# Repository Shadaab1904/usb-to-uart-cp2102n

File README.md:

# usb-to-uart-cp2102n
KiCad project: USB to UART converter based on CP2102N
This is a simple USB to UART converter board designed in **KiCad**, built around the **CP2102N** USB-to-Serial bridge IC.

## ✏️ About
This project converts USB signals to standard UART (TX, RX) levels, making it easy to interface a computer to microcontrollers, sensors, and other serial devices.  

It includes:
- CP2102N USB-to-UART IC
- USB connector (e.g., USB-C)
- Status LEDs (TX/RX)
- Filter capacitors
- UART header pins (TX, RX, , RST, GND, etc.)

## 📂 Project structure
- `USB TO UART.kicad_sch` – Schematic file
- `usb-to-uart.kicad_pcb` – PCB layout file
- `usb-to-uart.kicad_pro` – KiCad project file
- `symbols/` – Custom schematic symbols 
- `STEP/` - USB Type-C 3D Model
- `gerber/` – Gerber and drill files for fabrication
- `bom.csv` – Bill of Materials

- ## ⚙️ Tools
- Designed with [KiCad](https://kicad.org/)

- ## 📦 Fabrication
Use the files in the `gerber/` directory to order PCBs from manufacturers (e.g., JLCPCB etc.).

## 💡 Features
- CP2102N supports full-speed USB 2.0
- The CP2102N receives power from USB VBUS (5 V), connected to the REGIN pin. Its internal 3.3 V regulator outputs on VDD, with a 100 nF decoupling capacitor. This VDD rail powers the chip and defines the logic level for all UART signals (TX, RX, etc). Therefore, the UART interface operates at standard 3.3 V logic levels.
- Status LEDs for data transmission/reception
- Compact 2-layer PCB

- ## 📄 License
MIT License – feel free to modify and use.

## 🙌 Contributions
Pull requests welcome! If you spot issues or have improvements, please open an issue or PR.

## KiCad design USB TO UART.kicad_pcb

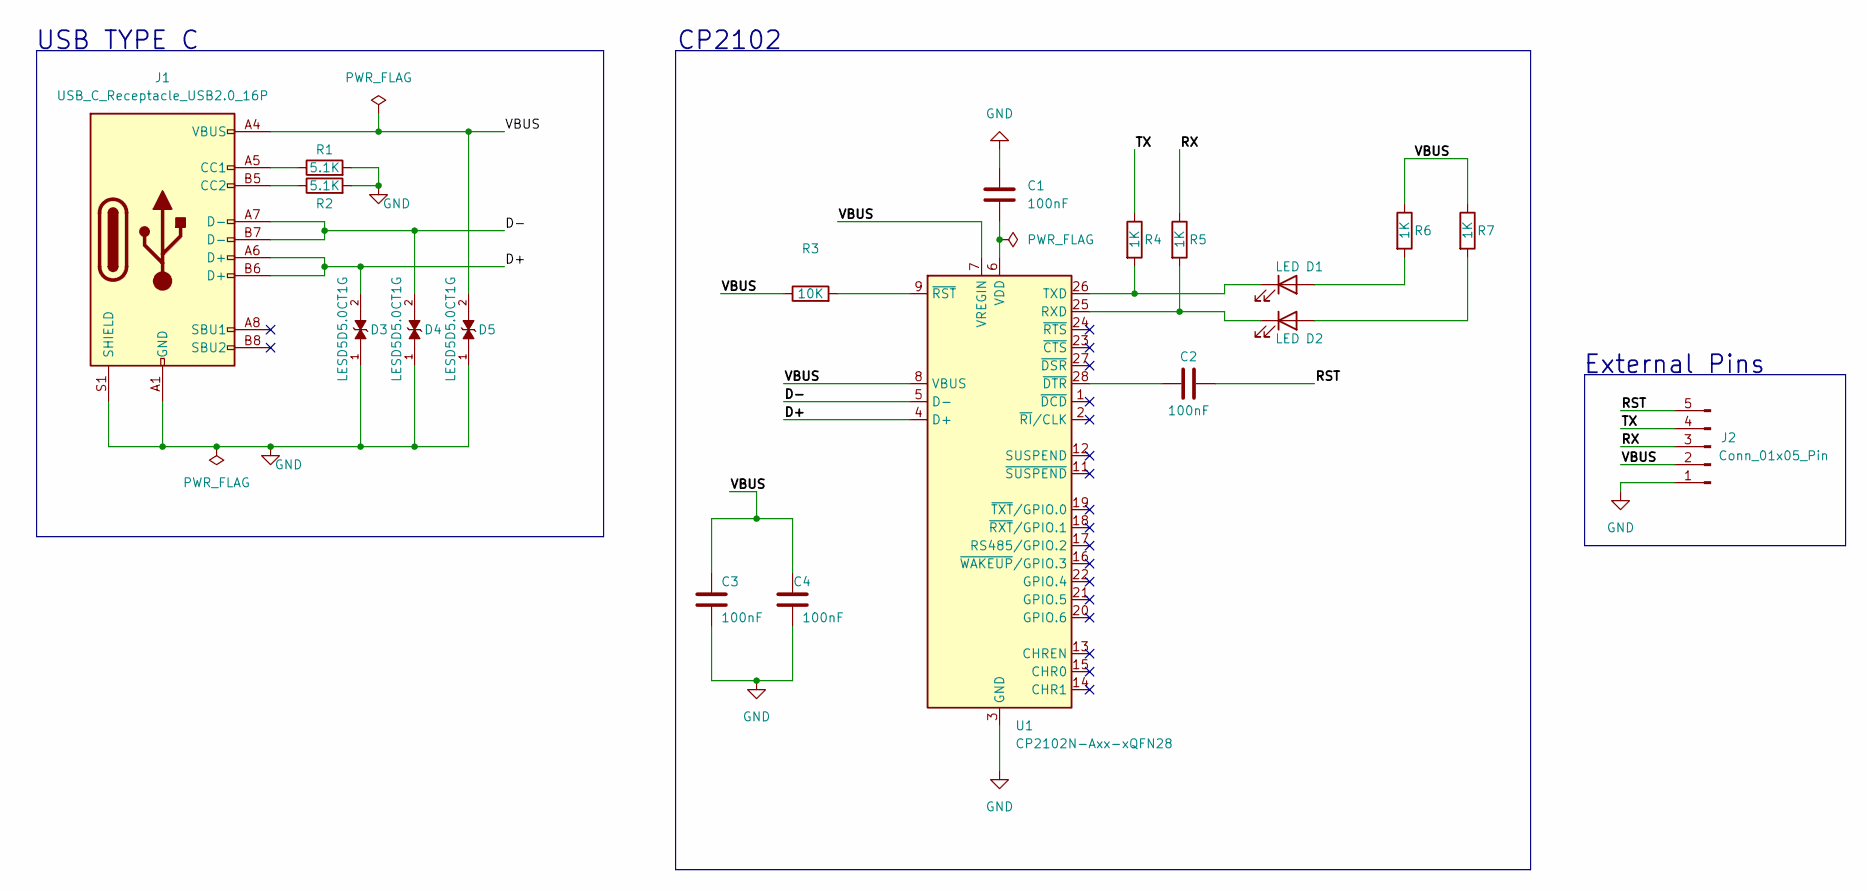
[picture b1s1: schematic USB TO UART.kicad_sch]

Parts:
C1, C2, C3, C4: 100nF; C_0805_2012Metric
D1, D2: LED; LED_0603_1608Metric
D3, D4, D5: LESD5D5.0CT1G; TVS_LESD5D5.0CT1G; PARTREV O
J1: USB_C_Receptacle_USB2.0_16P; USB_C_Receptacle_HRO_TYPE-C-31-M-12
J2: Conn_01x05_Pin; PinHeader_1x05_P2.54mm_Horizontal
R1, R2: 5.1K; R_0402_1005Metric
R3: 10K; R_0402_1005Metric
R4, R5, R6, R7: 1K; R_0402_1005Metric
U1: CP2102N-Axx-xQFN28; QFN-28-1EP_5x5mm_P0.5mm_EP3.35x3.35mm

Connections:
/D+: D3.2, J1.A6 (D+), J1.B6 (D+), U1.4 (D+)
/D-: D4.2, J1.A7 (D-), J1.B7 (D-), U1.5 (D-)
/RST: C2.2, J2.5
/RX: J2.3, R5.1
/TX: J2.4, R4.1
/VBUS: C3.1, C4.1, D5.2, J1.A4 (VBUS), J1.A9 (VBUS), J1.B4 (VBUS), J1.B9 (VBUS), J2.2, R3.1, R6.1, R7.1, U1.7 (VREGIN), U1.8 (VBUS)
GND: C1.1, C3.2, C4.2, D3.1, D4.1, D5.1, J1.A1 (GND), J1.A12 (GND), J1.B1 (GND), J1.B12 (GND), J1.S1 (SHIELD), J2.1, R1.2, R2.2, U1.3 (GND), U1.29 (GND)
unnamed: D1.2 (A), R6.2
unnamed: D1.1 (K), R4.2, U1.26 (TXD)
unnamed: D2.2 (A), R7.2
unnamed: D2.1 (K), R5.2, U1.25 (RXD)
unnamed: J1.A5 (CC1), R1.1
unnamed: J1.B5 (CC2), R2.1
unnamed: C1.2, U1.6 (VDD)
unnamed: C2.1, U1.28 (~DTR)
unnamed: R3.2, U1.9 (~RST)

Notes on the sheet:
USB TYPE C
External Pins
CP2102

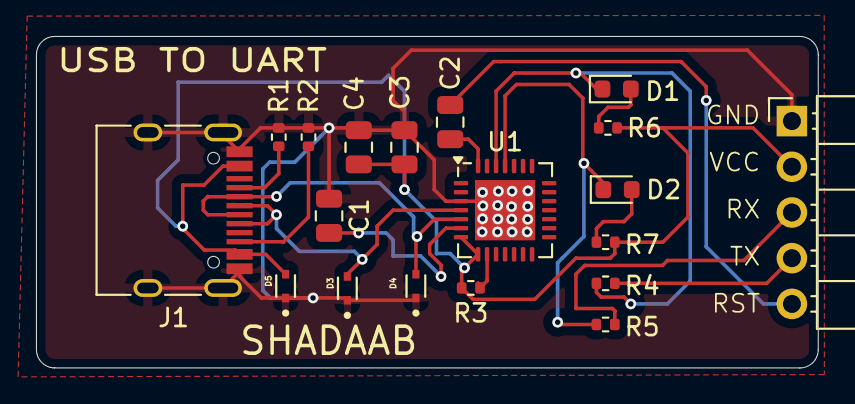
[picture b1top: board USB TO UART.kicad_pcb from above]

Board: 2 copper layers, 43.4 x 18.4 mm, 19 parts (0 on the bottom side), 16 nets.

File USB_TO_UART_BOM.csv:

"Reference","Qty","Value","DNP","Exclude from BOM","Exclude from Board","Footprint","Datasheet"
"C1,C2,C3,C4","4","100nF","","","","Capacitor_SMD:C_0805_2012Metric","~"
"D1,D2","2","LED","","","","LED_SMD:LED_0603_1608Metric","~"
"D3,D4,D5","3","LESD5D5.0CT1G","","","","LESD5D5.0CT1G:TVS_LESD5D5.0CT1G",""
"J1","1","USB_C_Receptacle_USB2.0_16P","","","","Connector_USB:USB_C_Receptacle_HRO_TYPE-C-31-M-12","https://www.usb.org/sites/default/files/documents/usb_type-c.zip"
"J2","1","Conn_01x05_Pin","","","","Connector_PinHeader_2.54mm:PinHeader_1x05_P2.54mm_Horizontal","~"
"R1,R2","2","5.1K","","","","Resistor_SMD:R_0402_1005Metric","~"
"R3","1","10K","","","","Resistor_SMD:R_0402_1005Metric","~"
"R4,R5,R6,R7","4","1K","","","","Resistor_SMD:R_0402_1005Metric","~"
"U1","1","CP2102N-Axx-xQFN28","","","","Package_DFN_QFN:QFN-28-1EP_5x5mm_P0.5mm_EP3.35x3.35mm","https://www.silabs.com/documents/public/data-sheets/cp2102n-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"

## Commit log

2025-07-16 Create USB 3D Model
2025-07-16 Create PCB_files
2025-07-16 Create temp
